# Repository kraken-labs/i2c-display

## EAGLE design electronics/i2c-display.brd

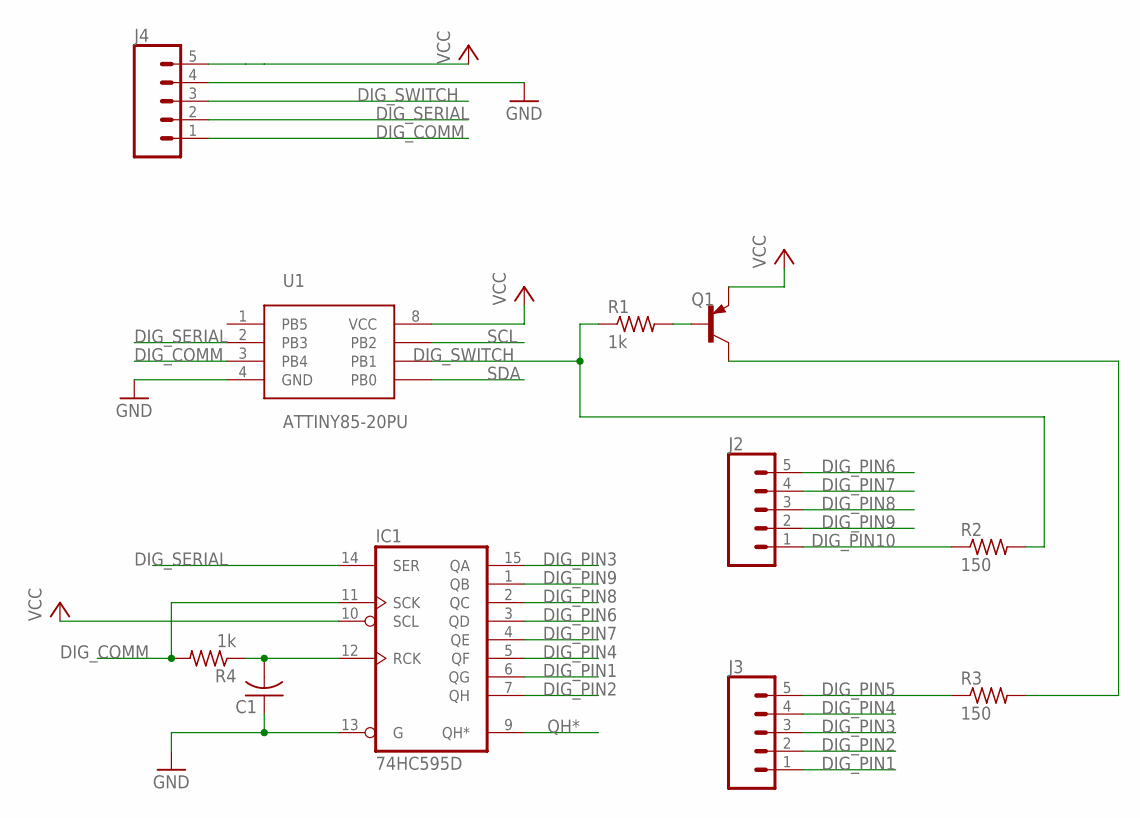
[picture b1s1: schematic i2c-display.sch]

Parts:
C1: C-USC0603; C0603
IC1: 74HC595D; SO16
J2, J3: CONN_05NO_SILK; 1X05_NO_SILK
J4: CONN_05; 1X05
Q1: BCX71SMD; SOT23
R1, R4: 1k; R0805
R2, R3: 150; R0805
U1: ATTINY85-20PU; PDIP-8

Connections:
DIG_COMM: IC1.11 (SCK), J4.1, R4.2, U1.3 (PB4)
DIG_PIN1: IC1.6 (QG), J3.1
DIG_PIN2: IC1.7 (QH), J3.2
DIG_PIN3: IC1.15 (QA), J3.3
DIG_PIN4: IC1.5 (QF), J3.4
DIG_PIN5: J3.5, R3.1
DIG_PIN6: IC1.3 (QD), J2.5
DIG_PIN7: IC1.4 (QE), J2.4
DIG_PIN8: IC1.2 (QC), J2.3
DIG_PIN9: IC1.1 (QB), J2.2
DIG_PIN10: J2.1, R2.1
DIG_SERIAL: IC1.14 (SER), J4.2, U1.2 (PB3)
DIG_SWITCH: J4.3, R1.1, R2.2, U1.6 (PB1)
GND: C1.1, IC1.8 (GND), IC1.13 (G), J4.4, U1.4 (GND)
unnamed: Q1.1 (B), R1.2
unnamed: Q1.3 (C), R3.2
unnamed: C1.2, R4.1
QH*: IC1.9 (QH*)
SCL: U1.7 (PB2)
SDA: U1.5 (PB0)
VCC: IC1.10 (SCL), IC1.16 (VCC), J4.5, Q1.2 (E), U1.8 (VCC)

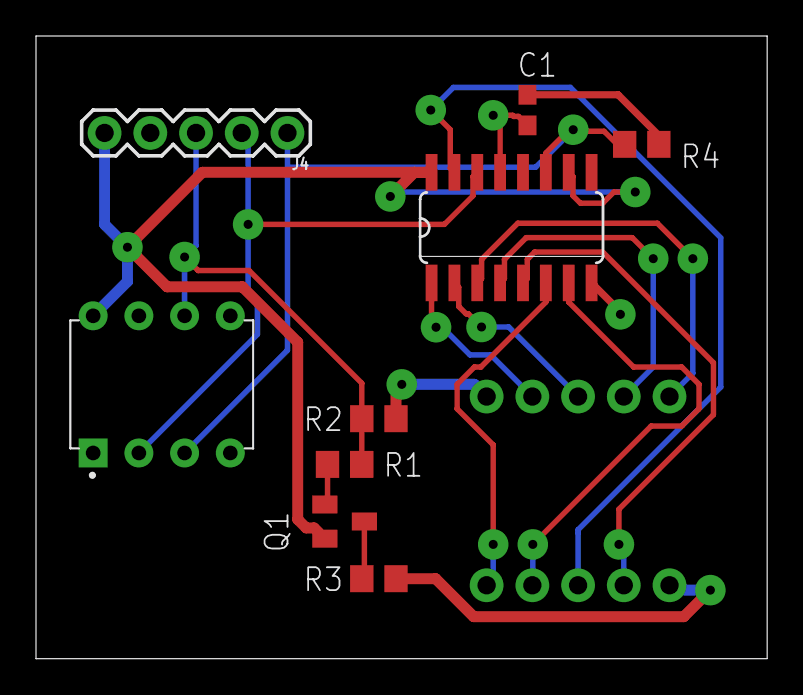
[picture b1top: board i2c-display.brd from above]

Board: 2 copper layers, 40.6 x 34.6 mm, 11 parts (0 on the bottom side), 18 nets.

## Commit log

2019-12-09 Added Eagle files
2019-12-09 Rendered board files

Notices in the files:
parts and their libraries:
SparkFun-Connectors: Licensing: Creative Commons ShareAlike 4.0 International - https://creativecommons.org/licenses/by-sa/4.0
